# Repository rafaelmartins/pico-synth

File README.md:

<!-- github-to-forgejo:notice:start -->
> [!IMPORTANT]
> Development has moved to [https://git.rafaelmartins.com/rafaelmartins/pico-synth](https://git.rafaelmartins.com/rafaelmartins/pico-synth). Please check [https://git.rafaelmartins.com/](https://git.rafaelmartins.com/) for details on how to contribute.
<!-- github-to-forgejo:notice:end -->

# pico-synth

A Raspberry Pi Pico based digital synthesizer.

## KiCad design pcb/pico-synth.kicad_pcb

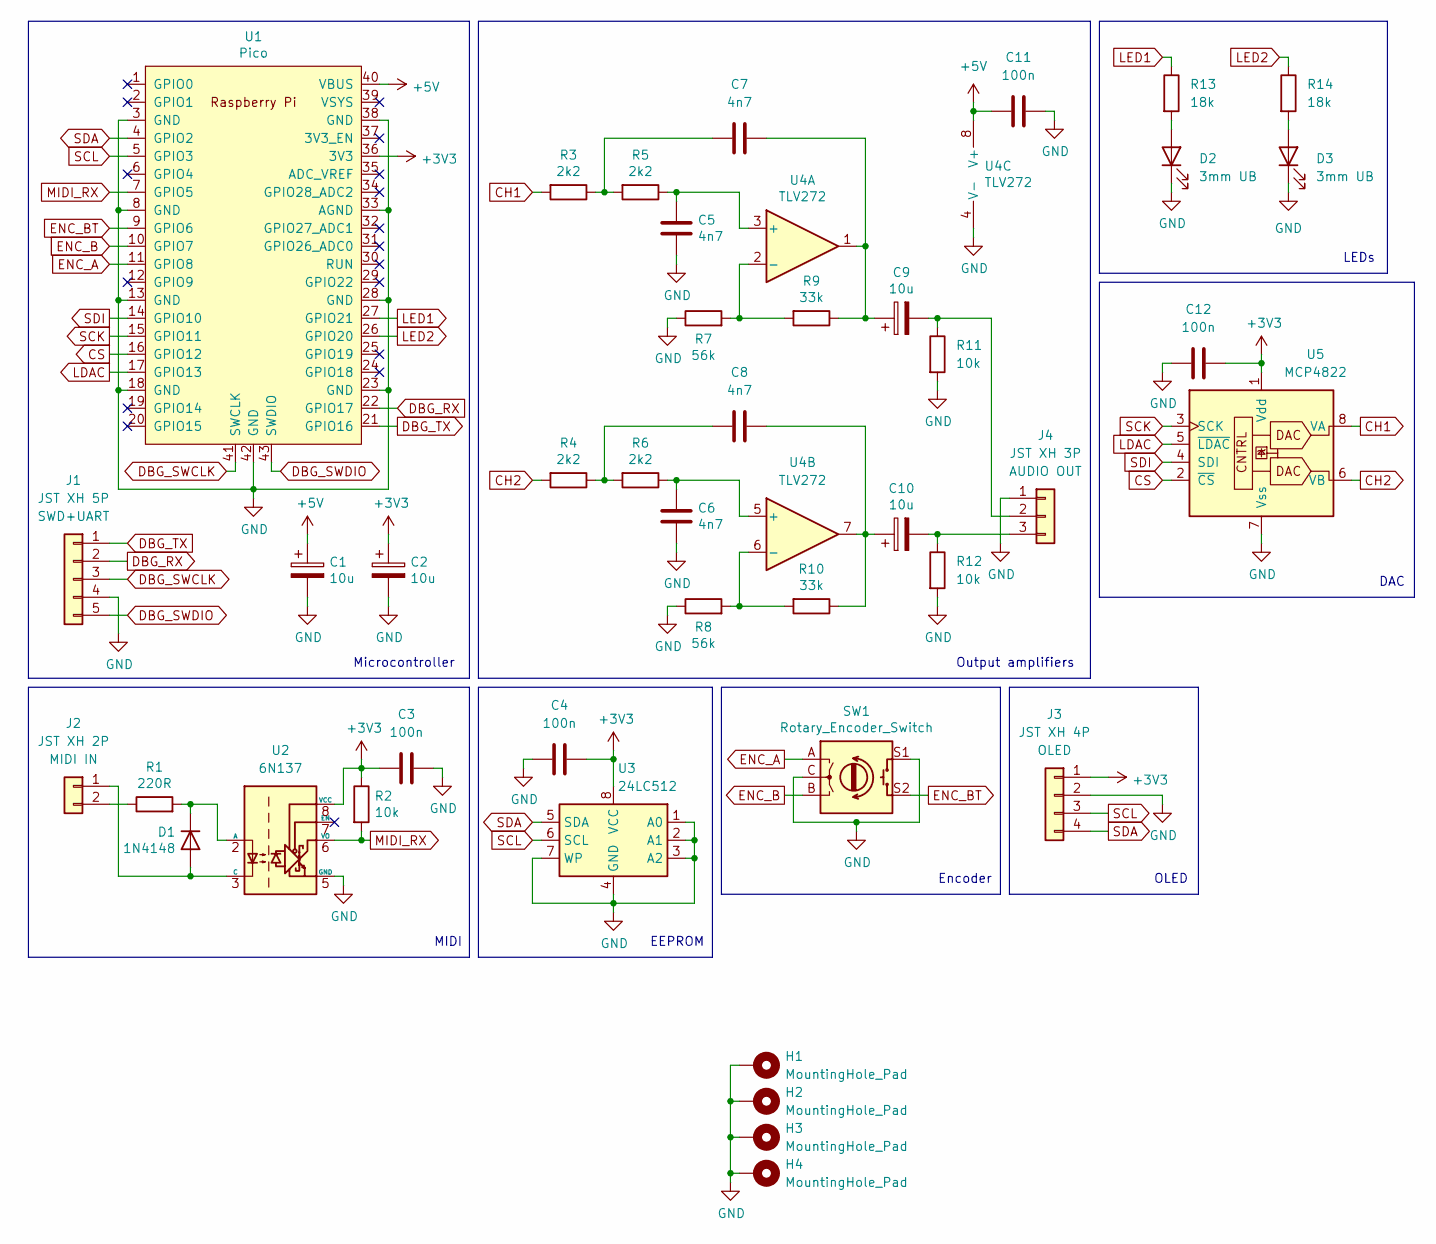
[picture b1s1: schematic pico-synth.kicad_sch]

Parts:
C1, C2, C9, C10: 10u; CP_Radial_D5.0mm_P2.50mm
C3, C4, C11, C12: 100n; C_Disc_D4.3mm_W1.9mm_P5.00mm
C5, C6, C7, C8: 4n7; C_Rect_L7.0mm_W2.5mm_P5.00mm
D1: 1N4148; D_DO-35_SOD27_P7.62mm_Horizontal
D2, D3: 3mm UB; LED_D3.0mm
H1, H2, H3, H4: MountingHole_Pad; MountingHole_2.2mm_M2_Pad_Via
J1: JST XH 5P; JST_XH_B5B-XH-A_PinSocket_1x05_P2.50mm_Vertical
J2: JST XH 2P; JST_XH_B2B-XH-A_PinSocket_1x02_P2.50mm_Vertical
J3: JST XH 4P; JST_XH_B4B-XH-A_PinSocket_1x04_P2.50mm_Vertical
J4: JST XH 3P; JST_XH_B3B-XH-A_PinSocket_1x03_P2.50mm_Vertical
R1: 220R; R_Axial_DIN0207_L6.3mm_D2.5mm_P10.16mm_Horizontal
R2, R11, R12: 10k; R_Axial_DIN0207_L6.3mm_D2.5mm_P10.16mm_Horizontal
R3, R4, R5, R6: 2k2; R_Axial_DIN0207_L6.3mm_D2.5mm_P10.16mm_Horizontal
R7, R8: 56k; R_Axial_DIN0207_L6.3mm_D2.5mm_P10.16mm_Horizontal
R9, R10: 33k; R_Axial_DIN0207_L6.3mm_D2.5mm_P10.16mm_Horizontal
R13, R14: 18k; R_Axial_DIN0207_L6.3mm_D2.5mm_P10.16mm_Horizontal
SW1: Rotary_Encoder_Switch; RotaryEncoder_Alps_EC11E-Switch_Vertical_H20mm_CircularMoun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
U1: Pico; RPi_Pico_SMD_TH
U2: 6N137; DIP-8_W7.62mm
U3: 24LC512; DIP-8_W7.62mm
U4: TLV272; DIP-8_W7.62mm
U5: MCP4822; DIP-8_W7.62mm

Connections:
+3V3: C2.1, C3.1, C4.2, C12.2, J3.1, R2.1, U1.36 (3V3), U2.8 (VCC), U3.8 (VCC), U5.1 (Vdd)
+5V: C1.1, C11.1, U1.40 (VBUS), U4.8 (V+)
CH1: R3.2, U5.8 (VA)
CH2: R4.2, U5.6 (VB)
CS: U1.16 (GPIO12), U5.2 (~CS)
DBG_RX: J1.2, U1.22 (GPIO17)
DBG_SWCLK: J1.3, U1.41 (SWCLK)
DBG_SWDIO: J1.5, U1.43 (SWDIO)
DBG_TX: J1.1, U1.21 (GPIO16)
ENC_A: SW1.A, U1.11 (GPIO8)
ENC_B: SW1.B, U1.10 (GPIO7)
ENC_BT: SW1.S2, U1.9 (GPIO6)
GND: C1.2, C2.2, C3.2, C4.1, C5.2, C6.2, C11.2, C12.1, D2.1 (K), D3.1 (K), H1.1, H2.1, H3.1, H4.1, J1.4, J3.2, J4.1, R7.1, R8.1, R11.2, R12.2, SW1.C, SW1.S1, U1.3 (GND), U1.8 (GND), U1.13 (GND), U1.18 (GND), U1.23 (GND), U1.28 (GND), U1.33 (AGND), U1.38 (GND), U1.42 (GND), U2.5 (GND), U3.1 (A0), U3.2 (A1), U3.3 (A2), U3.4 (GND), U3.7 (WP), U4.4 (V-), U5.7 (Vss)
LDAC: U1.17 (GPIO13), U5.5 (~LDAC)
LED1: R13.1, U1.27 (GPIO21)
LED2: R14.1, U1.26 (GPIO20)
MIDI_RX: R2.2, U1.7 (GPIO5), U2.6 (VO)
unnamed: C5.1, R5.1, U4.3 (+)
unnamed: C6.1, R6.1, U4.5 (+)
unnamed: C7.1, R3.1, R5.2
unnamed: C7.2, C9.1, R9.1, U4.1
unnamed: C8.1, R4.1, R6.2
unnamed: C9.2, J4.2, R11.1
unnamed: C8.2, C10.1, R10.1, U4.7
unnamed: C10.2, J4.3, R12.1
unnamed: D1.1 (K), R1.2, U2.2 (A)
unnamed: D1.2 (A), J2.1, U2.3 (C)
unnamed: D2.2 (A), R13.2
unnamed: D3.2 (A), R14.2
unnamed: J2.2, R1.1
unnamed: R7.2, R9.2, U4.2 (-)
unnamed: R8.2, R10.2, U4.6 (-)
SCK: U1.15 (GPIO11), U5.3 (SCK)
SCL: J3.3, U1.5 (GPIO3), U3.6 (SCL)
SDA: J3.4, U1.4 (GPIO2), U3.5 (SDA)
SDI: U1.14 (GPIO10), U5.4 (SDI)

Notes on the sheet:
EEPROM
Output amplifiers
LEDs
OLED
Encoder
Microcontroller
MIDI
DAC

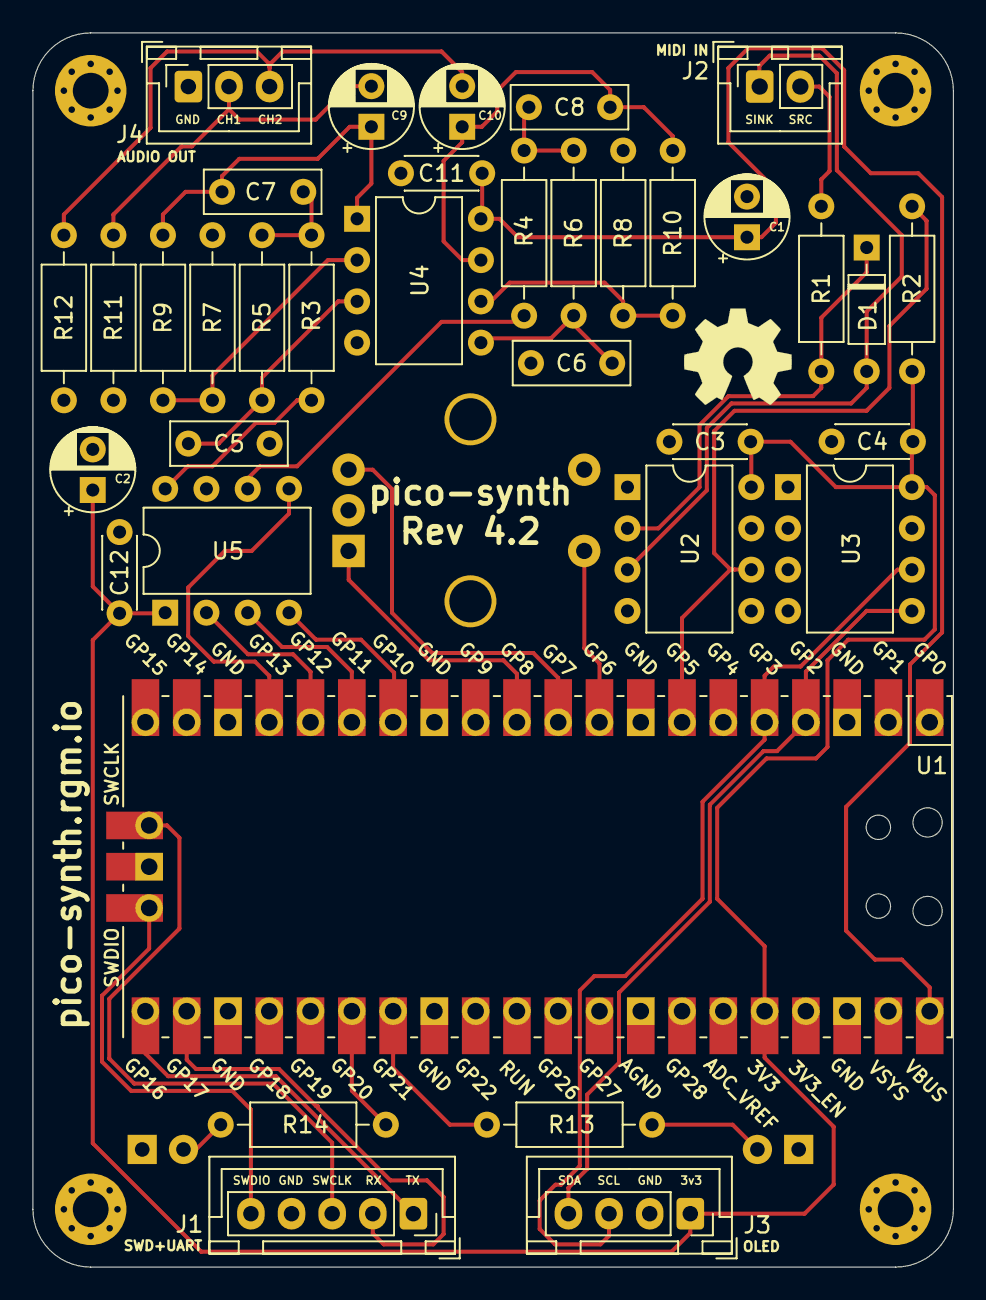
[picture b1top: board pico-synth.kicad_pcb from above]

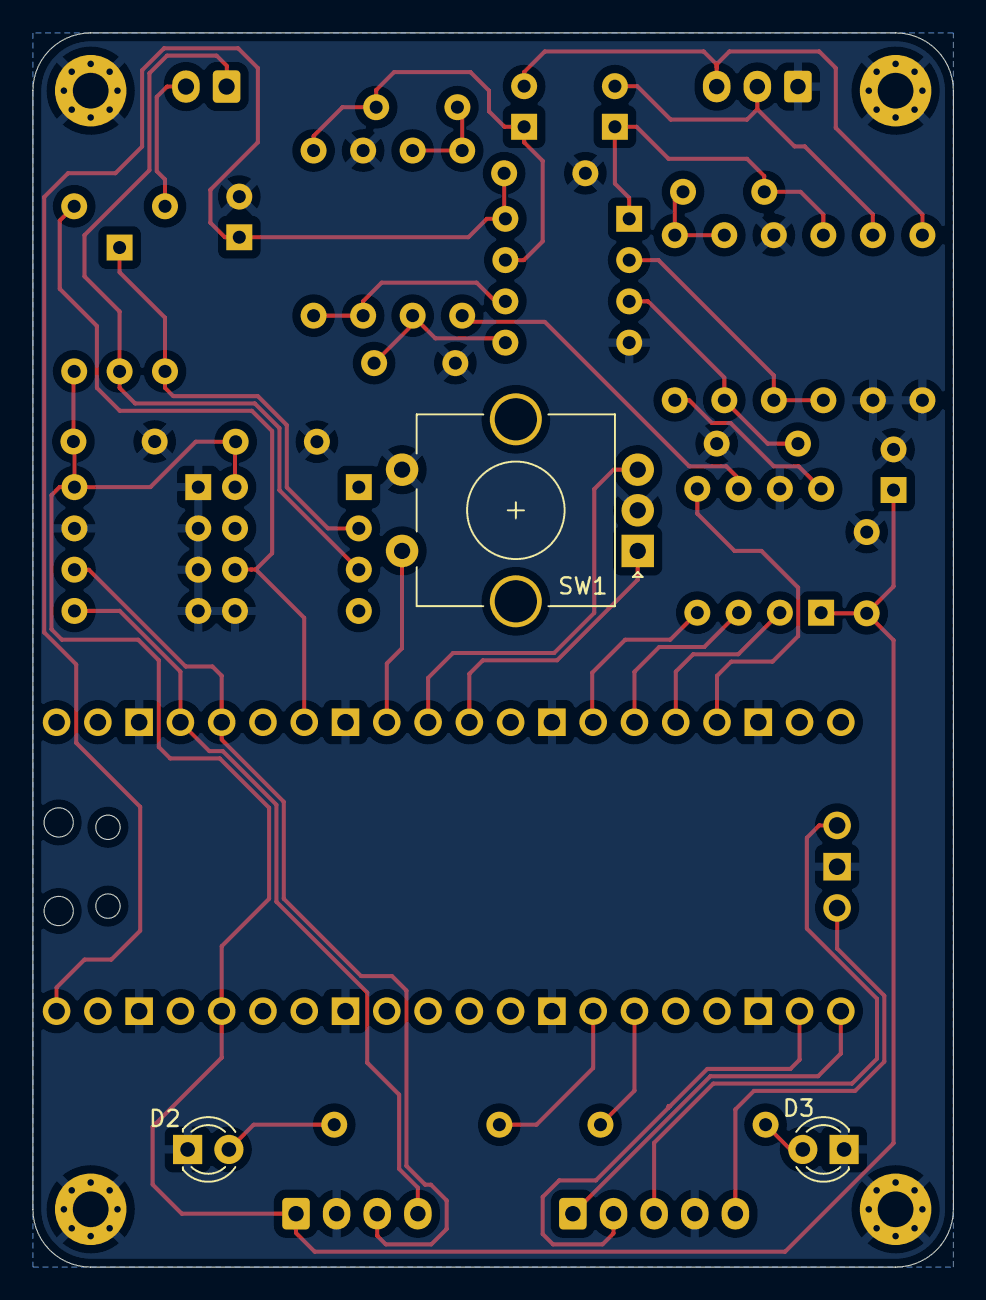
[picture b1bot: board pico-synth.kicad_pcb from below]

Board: 2 copper layers, 56.6 x 75.9 mm, 43 parts (3 on the bottom side), 36 nets.

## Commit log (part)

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2021-06-07 *: oscillator simplification (incomplete). allow using single dac
2021-06-07 mcp4822: oscillator: waveform: use int16_t for samples
    this makes it easier for our future envelopes/filters/effects to work
    with the samples.
2021-06-07 note: avoid hardcoding last note
2021-06-07 phase: simplify code
2021-06-07 mcp4822: clip samples if exceeded hardware range
2021-06-08 usb: use flash unique id as serial number
2021-06-08 controller: midi changes for tinyusb-0.10.1/pico-sdk-1.2.0
2021-06-18 main: updates for new prototype, bare minimum that compiles
2021-06-18 added new oled text user interface library
2021-06-18 added ec11-like encoder library. not used yet
2021-06-19 added midi library. not used yet
2021-06-19 midi: reset data after callback call
2021-07-04 added eeprom-i2c (24LC256) library. not used yet
2021-07-04 oscillator: improvements
2021-07-30 ec11: optimize state machine
2021-08-04 oled-tui: support cleaning one line
2021-08-08 eeprom-i2c: support 24LC512
2021-08-08 main: mcp4822: rewrite base synth logic
2021-08-14 synth: offload sample evaluation from core1
2022-01-29 move source code to firmware directory
2022-01-29 added main enclosure 3d model
2022-01-29 added kicad project for hardware revision 2.0
    this was already fabricated. gerber included.
2022-02-01 new hardware revision: 2.1
    this adds a two leds, for output monitoring
2022-02-11 3d-models: update enclosure
2022-02-11 3d-models: added led holder
2022-02-11 firmware: added oled-tui menu
2022-04-05 pcb: upgrade to kicad 6
2022-04-08 pcb: added new revision 2.2
    trying to avoid using dc-dc charge pump
2022-04-11 new hardware revision: 3.0
    - added better output filter (Sallen-Key low pass filter)
    - use MCP4822's LDAC pin to avoid (minimal, negligible :) phase drift
    between the channels
2022-04-11 firmware: initial voice settings. support dynamic tui lines
2022-04-11 firmware: some openocd/gdb settings
2022-04-11 firmware: engine: added lookup tables and generated data
2022-04-11 firmware: engine: added initial engine implementation
2022-04-11 firmware: starting rewrite
2022-04-11 tui: added basic screen implementation
2022-04-11 firmware: tui: basic drivers
2022-04-11 firmware: engine: added mcp4822 driver
2022-04-11 firmware: engine: added initial oscillator module
2022-04-11 firmware: centralize screen implementations
2022-04-11 firmware: engine: generate missing include
2022-04-11 firmware: engine: mcp4822: support ldac pin
2022-04-15 firmware: engine: split modules into source and filters
2022-04-15 firmware: midi: initial midi implementation
2022-04-15 firmware: engine: oscillator: remove unset note, add sync
    note duration should be handled afterwards by a gate or envelope.
    also includes other minor improvements.
2022-04-15 firmware: engine: amplifier: initial implementation
2022-04-23 firmware: engine: use bandlimited wavetables
    this helps to reduce aliasing when synthesizing waveforms. sawtooths
    still have some aliasing. should be fixed later with some interpolation.
2022-04-23 firmware: engine: use frequency instead of blit avg for C4
    the reference paper says that C4 is the average value of the blit, but
    also says that it is a frequency function, then I tried to set it to
    a frequency 1/T, which yields waveforms with way less aliasing.
2022-04-23 firmware: engine: interpolate samples
2022-04-26 firmware: engine: amplifier: hold mutex in sample func
2022-04-29 3d-models: update enclosure model for PCB revision 4.0
2022-04-29 pcb: new hardware revision: 4.0
2022-05-06 pcb: remove old schematic cache library
2022-05-06 pcb: remove local kicad project settings
2022-05-08 firmware: adapt to hardware revision 4.0
2022-05-08 firmware: engine: mixer: initial implementation
    this adds basic polyphony support. no midi support yet.
2022-05-09 firmware: implement some basic midi polyphony
    maybe my ears are tired, but it sounds slightly detuned
2022-05-09 firmware: engine: support running without sink
    in this case only one voice per channel is supported, and the end of the
    filter chain is plugged directly to output
2022-05-10 firmware: engine: rename ps_engine_t::channel to plural
2022-05-10 firmware: rewrite channel implementation
    implement only one voice per channel for now. may stick with that, though.
2022-05-11 firmware: use leds for channel gates
2022-05-16 firmware: fix stdio struct naming
2022-05-16 firmware: midi: rewrite usb descriptors
2022-05-19 firmware: split core0 init, to fix uart for core1
2022-05-23 firmware: engine: oscillator: avoid changing frequency mid-cycle
    this removes the sync functionality for now
2022-05-23 firmware: engine: amplifier: implement a state machine for gate state
2022-05-23 main: avoid compiler warning
2022-05-28 firmware: midi: rewrite midi parser
2022-05-28 firmware: midi: make usb descriptors configurable
2022-06-06 build: generate bom html
2022-06-06 *: add license headers
2022-06-07 midi: use openmoko provided USB PIDs
2022-06-09 firmware: engine: improve phase type
2022-06-10 firmware: engine: minor fixes
2022-06-10 firmware: engine: add ADSR envelope module
2022-06-10 firmware: engine: adsr: exit when changing state to off
2022-06-11 firmware: midi: make message union unnamed
2022-06-11 firmware: tui: make unions unnamed
2022-06-11 firmware: tui: improve line callbacks
2022-06-11 firmware: tui: add function to reload current screen
2022-06-11 firmware: settings: add missing pragma
2022-06-11 firmware: synth: use synth_t as context data
2022-06-12 firmware: tui: eeprom driver improvements
2022-06-13 firmware: midi: avoid global variables
2022-06-19 firmware: tui: rename most "callback" occurences to "func"
2022-06-19 firmware: midi: enable uart fifo, otherwise delayed event is lost
2022-06-19 firmware: tui: added select_byte screen type
2022-06-21 firmware: engine: simplify step definitions
2022-06-21 firmware: added basic eeprom preset support and ui screens
    most of the ui is implemented, missing:
    - preset name editing (must implement a screen type to edit strings).
    - eeprom save and eeprom clean actions (maybe implement a confirmation
    screen type).
2022-06-21 firmware: tui: allow lazy eeprom writes
2022-06-21 firmware: support saving settings to eeprom
2022-06-21 firmware: support erasing settings from eeprom
2022-06-21 firmware: tui: improve menus and select screens
2022-06-21 firmware: tui: always reboot after eeprom erase
2022-06-24 firmware: tui: add screens with automated (delayed) action
2022-06-24 firmware: tui: allow using select_byte screen as notification
2022-06-24 firmware: implement adsr control via midi
2022-06-26 firmware: implement oscillator waveform control via midi
2022-07-01 pcb: new hardware revision: 4.2
2024-09-24 firmware: build extra binary types
2024-09-24 build: add simple workflow to build binaries for each commit
2024-09-24 build: dist: fix source dir and PICO_SDK_PATH

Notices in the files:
pcb/pico-synth.kicad_sch:
Released under CERN Open Hardware Licence Version 2 - Strongly Reciprocal
